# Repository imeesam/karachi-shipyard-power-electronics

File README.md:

# Power Electronics & PCB Design Portfolio

**Hardware Engineering Projects | Karachi Shipyard & Engineering Works (KSEW)**

This repository contains schematic capture, PCB layout, and 3D mechanical render files for two custom power electronics boards developed at **Karachi Shipyard & Engineering Works (KSEW)**.

## Repository Structure

```text
AC to DC Conveter/
├── docs/
│   ├── 3D_back.png
│   ├── 3D_front.png
│   ├── Routing.png
│   └── Schematic.png
└── AC_DC_converter.*

Power Supply/
├── docs/
│   ├── back.jpg
│   ├── Front.jpg
│   └── side.jpg
└── transformerlesspowersupply.*

.gitignore
LICENSE
README.md
```

## 12 V AC-to-DC Bridge Rectifier Converter

A compact, single-layer, through-hole full-wave bridge rectifier and capacitive filter module designed to convert a 12 V AC input into a smoothed DC output with visual power indication and bleeder discharge protection.

### Bill of Materials

| Reference | Component | Value or part number | Role |
| --- | --- | --- | --- |
| J1, J2 | Screw terminals | `Screw_Terminal_01x02` | 12 V AC input and filtered DC output |
| D1-D4 | Rectifier diodes | `1N4007` (×4) | Full-wave bridge rectification |
| C1 | Electrolytic capacitor | `1000 µF` | Output ripple filtering and DC smoothing |
| R1 | Current-limiting resistor | `2.2 kΩ` | Limits current through the indicator LED |
| R2 | Bleeder resistor | `10 kΩ` | Discharges C1 when power is removed |
| D5 | Indicator LED | Standard LED | Indicates DC output power |

### Schematic and PCB Preview

| Schematic | PCB Routing |
| --- | --- |
|  |  |

| 3D Front View | 3D Back View |
| --- | --- |
|  |  |

## Transformerless Regulated Power Supply

A compact capacitive-dropper regulated DC power supply PCB for low-power auxiliary and control electronics, without the footprint or weight of a step-down transformer.

### Design Highlights

- **Capacitive dropper:** High-voltage X2 film capacitor paired with series surge-limiting and discharge resistors.
- **Rectification and filtering:** Discrete rectifier stage with dual electrolytic smoothing capacitors.
- **Linear voltage regulation:** TO-220 package regulator providing a stable DC rail to the output screw terminal block.
- **Status indication:** On-board power indicator LED and 2-pin screw terminals for AC mains input and regulated DC output.

> [!WARNING]
> Transformerless power supplies are **not galvanically isolated** from the AC mains. Keep the board inside a fully insulated enclosure and avoid touching conductive traces or components while energized.

### Mechanical Previews

| Top / Front View | Bottom / Solder Side | Side Profile |
| --- | --- | --- |
|  |  |  |

## Getting Started

1. Clone the repository:

   ```bash
   git clone https://github.com/imeesam/karachi-shipyard-power-electronics.git
   cd karachi-shipyard-power-electronics
   ```

1. **Clone the repository:**
```bash
git clone (https://github.com/imeesam/karachi-shipyard-power-electronics.git)
```

2. Open a project in KiCad:

   - Open `AC_DC_converter.kicad_pro` in `AC to DC Conveter/`.
   - Open `transformerlesspowersupply.kicad_pro` in `Power Supply/`.

3. Inspect or manufacture:

   - View schematics in the Schematic Editor.
   - Inspect track widths and clearances in the PCB Editor.
   - Export Gerber and drill files for fabrication.

## KiCad

The projects were created with KiCad. KiCad 6.0 or later is recommended.

## Author
**Meesam Abbas**
Power Electronics & PCB Design - Karachi Shipyard & Engineering Works (KSEW)

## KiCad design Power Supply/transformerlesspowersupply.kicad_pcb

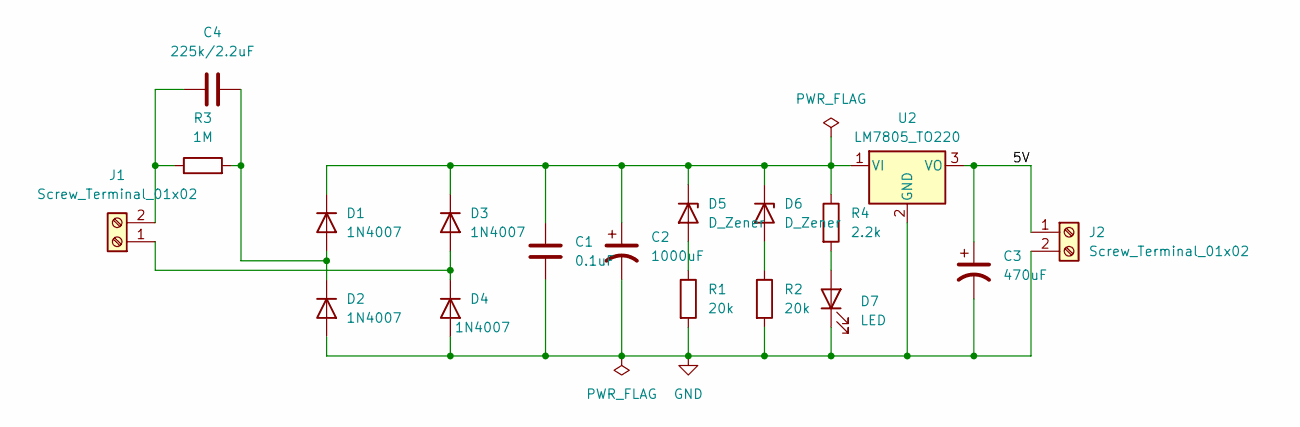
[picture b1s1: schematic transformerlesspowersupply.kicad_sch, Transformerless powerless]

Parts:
C1: 0.1uF; C_Disc_D4.7mm_W2.5mm_P5.00mm
C2: 1000uF; CP_Radial_D10.0mm_P5.00mm
C3: 470uF; CP_Radial_D10.0mm_P3.80mm
C4: 225k/2.2uF; C_Rect_L18.0mm_W6.0mm_P15.00mm_FKS3_FKP3
D1, D2, D3, D4: 1N4007; D_DO-41_SOD81_P10.16mm_Horizontal
D5, D6: D_Zener; D_A-405_P7.62mm_Horizontal
D7: LED; LED_D3.0mm
J1, J2: Screw_Terminal_01x02; TerminalBlock_bornier-2_P5.08mm
R1, R2: 20k; R_Axial_DIN0207_L6.3mm_D2.5mm_P7.62mm_Horizontal
R3: 1M; R_Axial_DIN0207_L6.3mm_D2.5mm_P7.62mm_Horizontal
R4: 2.2k; R_Axial_DIN0207_L6.3mm_D2.5mm_P7.62mm_Horizontal
U2: LM7805_TO220; TO-220-3_Vertical

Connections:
/5V: C3.1, J2.1, U2.3 (VO)
GND: C1.2, C2.2, C3.2, D2.2 (A), D4.2 (A), D7.1 (K), J2.2, R1.2, R2.2, U2.2 (GND)
unnamed: C4.2, D1.2 (A), D2.1 (K), R3.2
unnamed: C1.1, C2.1, D1.1 (K), D3.1 (K), D5.1 (K), D6.1 (K), R4.1, U2.1 (VI)
unnamed: D3.2 (A), D4.1 (K), J1.1
unnamed: D5.2 (A), R1.1
unnamed: D6.2 (A), R2.1
unnamed: D7.2 (A), R4.2
unnamed: C4.1, J1.2, R3.1

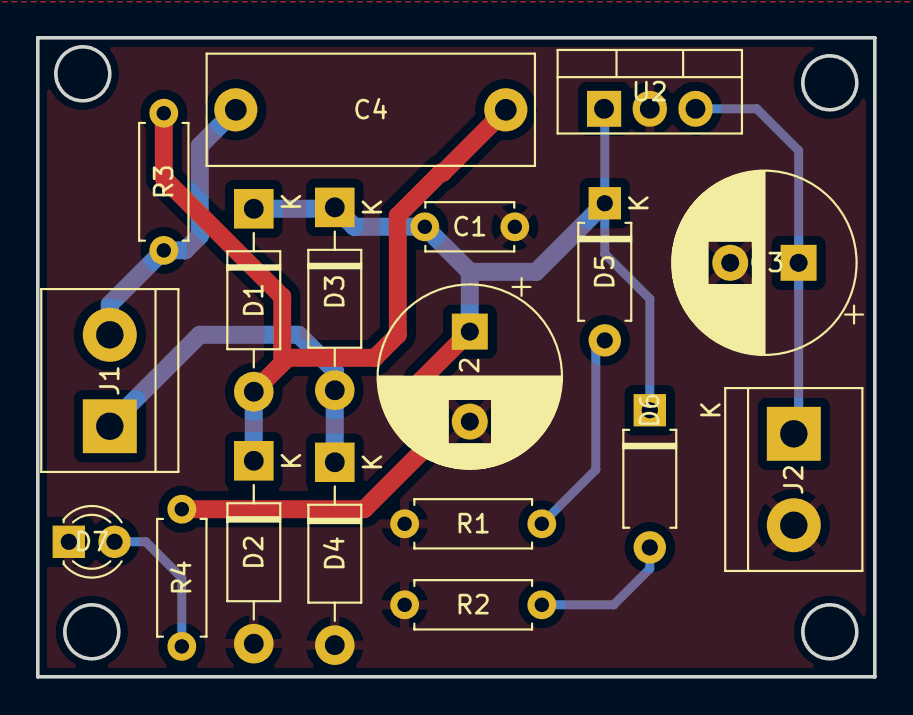
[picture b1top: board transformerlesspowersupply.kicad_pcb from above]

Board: 2 copper layers, 46.5 x 35.5 mm, 18 parts (0 on the bottom side), 9 nets.

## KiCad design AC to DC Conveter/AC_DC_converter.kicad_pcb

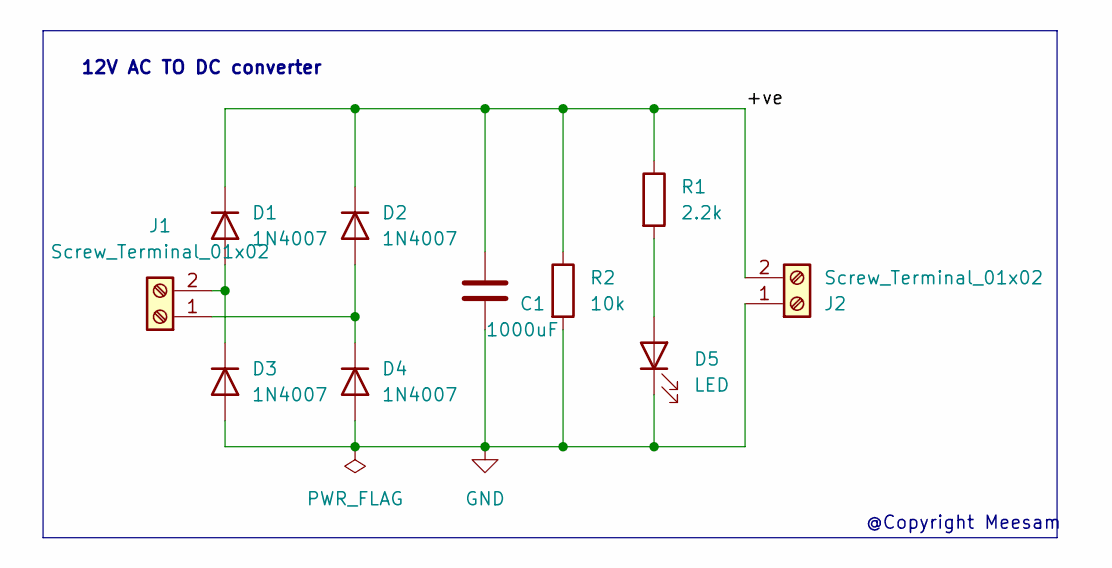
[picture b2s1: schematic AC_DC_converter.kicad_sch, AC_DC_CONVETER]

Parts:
C1: 1000uF; C_Radial_D8.0mm_H11.5mm_P3.50mm
D1, D2, D3, D4: 1N4007; D_DO-41_SOD81_P10.16mm_Horizontal
D5: LED; LED_D5.0mm
J1, J2: Screw_Terminal_01x02; TerminalBlock_bornier-2_P5.08mm
R1: 2.2k; R_Axial_DIN0204_L3.6mm_D1.6mm_P7.62mm_Horizontal
R2: 10k; R_Axial_DIN0204_L3.6mm_D1.6mm_P7.62mm_Horizontal

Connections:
/+ve: C1.2, D1.1 (K), D2.1 (K), J2.2, R1.1, R2.1
GND: C1.1, D3.2 (A), D4.2 (A), D5.1 (K), J2.1, R2.2
unnamed: D1.2 (A), D3.1 (K), J1.2
unnamed: D2.2 (A), D4.1 (K), J1.1
unnamed: D5.2 (A), R1.2

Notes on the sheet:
@Copyright Meesam
12V AC TO DC converter

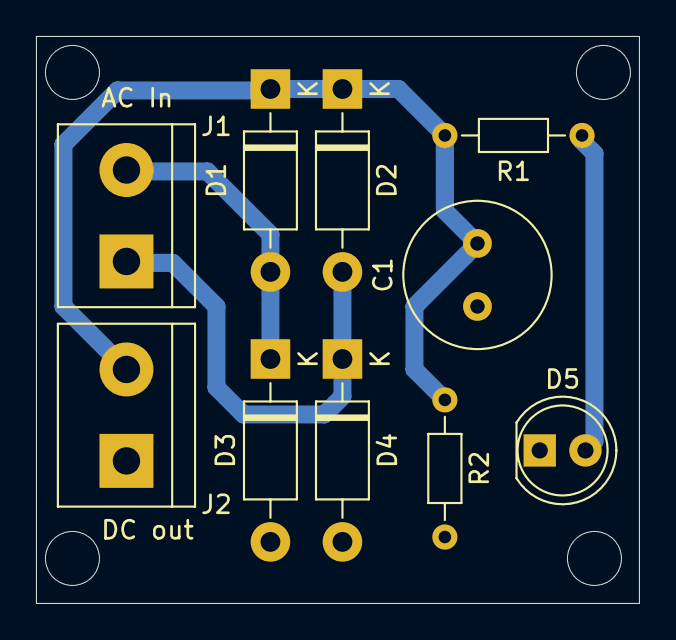
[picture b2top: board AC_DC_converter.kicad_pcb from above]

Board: 2 copper layers, 33.5 x 31.5 mm, 10 parts (0 on the bottom side), 5 nets.

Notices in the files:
AC to DC Conveter/AC_DC_converter.kicad_pcb:
©Copyright Meesam
README.md:
License: MIT
